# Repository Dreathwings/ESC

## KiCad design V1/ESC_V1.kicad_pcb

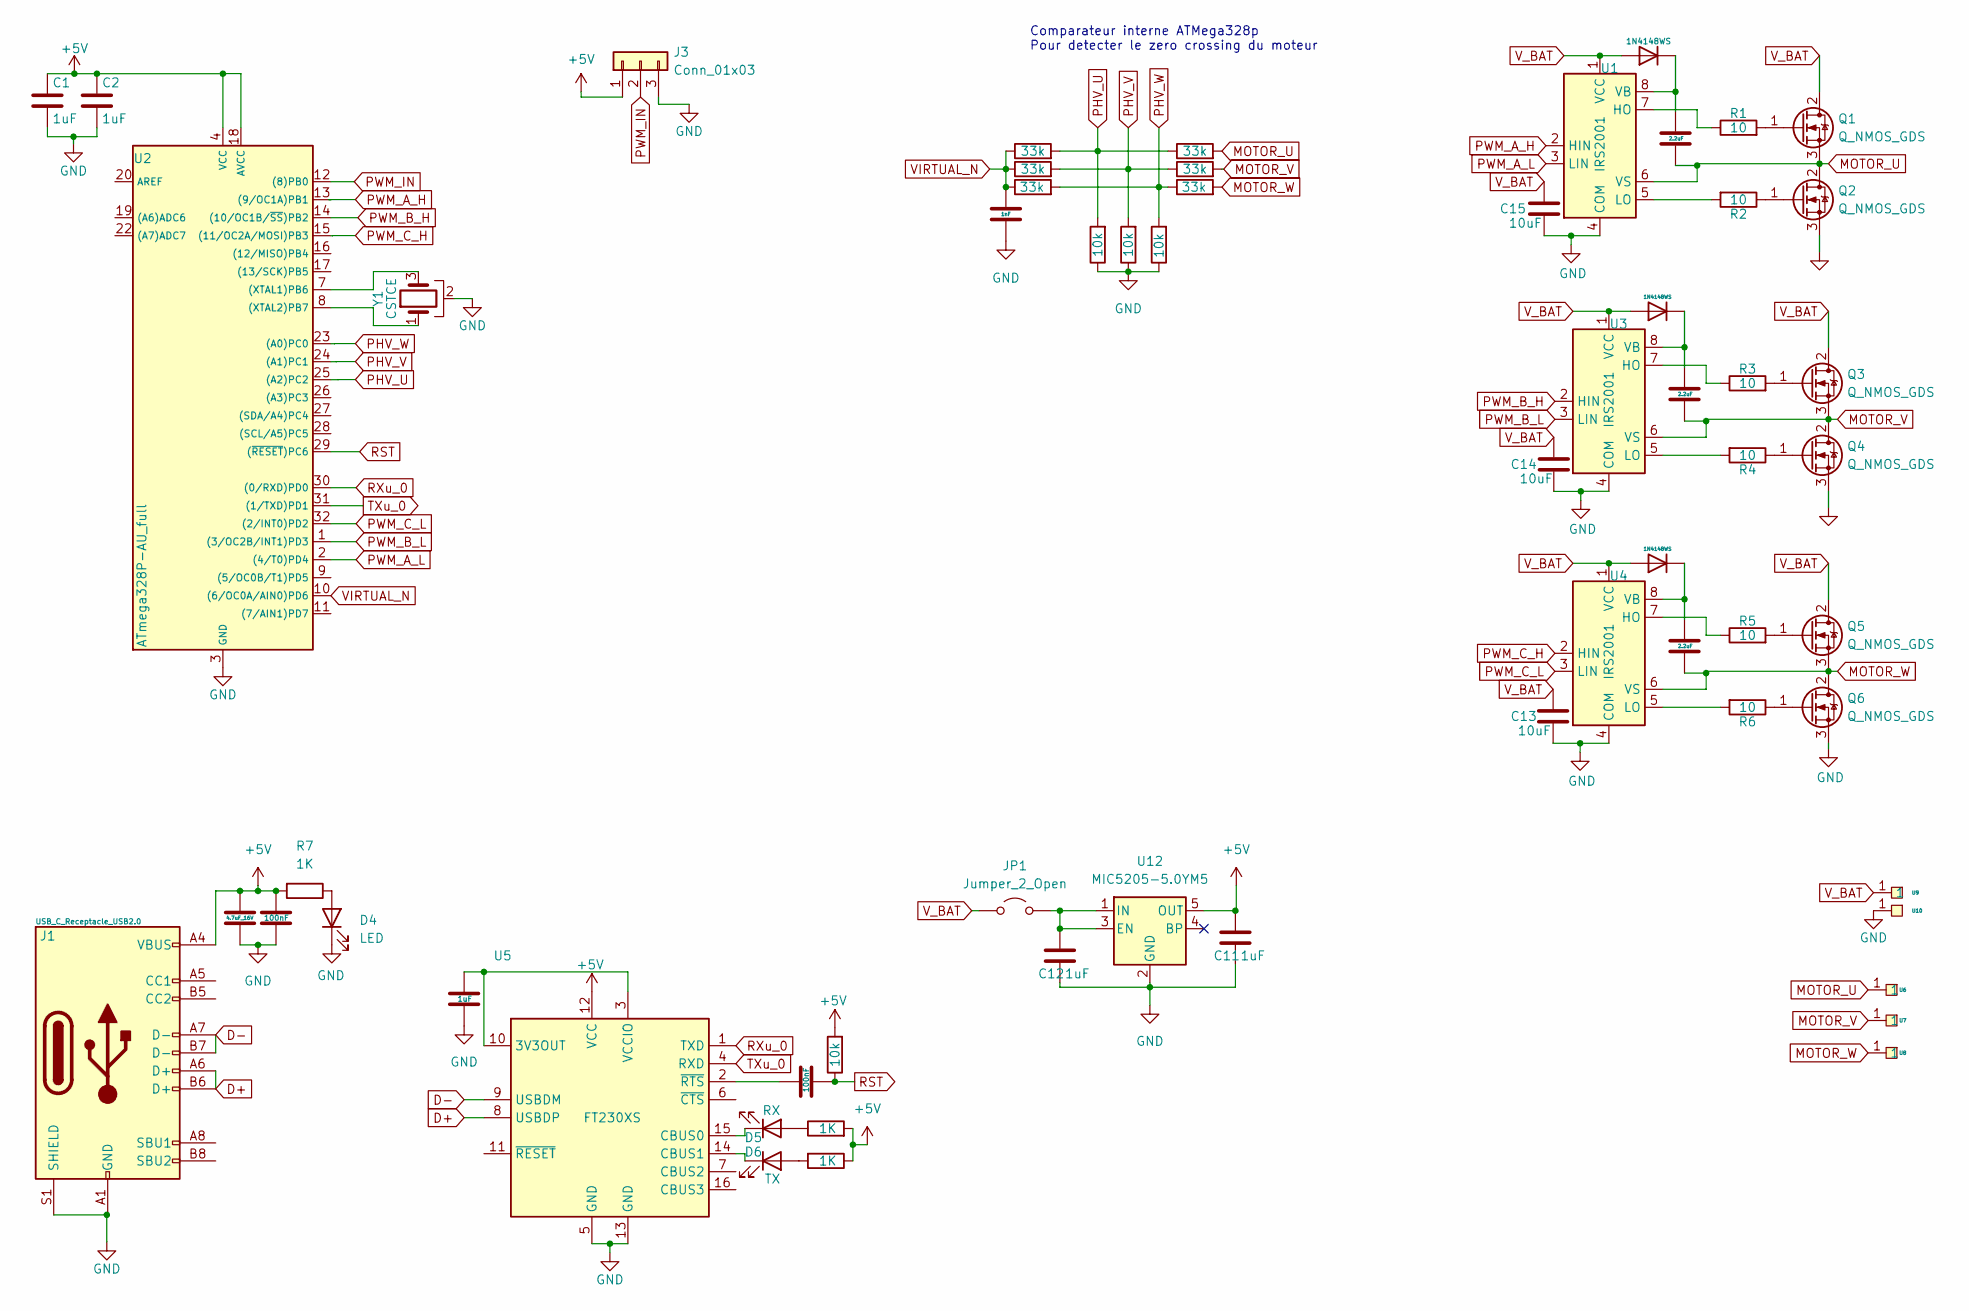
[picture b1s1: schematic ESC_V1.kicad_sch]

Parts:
C1, C2, C11, C12: 1uF; 0603
C3, C4, C5: 2.2uF; 1206
C6: 1uF; 1206
C7, C9: 100nF; 1206
C8: 4.7uF_16V; 1206
C10: 1nF; 1206
C13, C14, C15: 10uF; 1206
D1, D2, D3: 1N4148WS; 1206
D4: LED; 1206
D5: RX; LED_0603_1608Metric
D6: TX; LED_0603_1608Metric
J1: USB_C_Receptacle_USB2.0; USB-C USB4110_GCT
J3: Conn_01x03; PinSocket_1x03_P2.54mm_Horizontal
JP1: Jumper_2_Open; TestPoint_2Pads_Pitch2.54mm_Drill0.8mm
Q1, Q2, Q3, Q4, Q5, Q6: Q_NMOS_GDS; TO-263-2
R1, R2, R3, R4, R5, R6: 10; 1206
R7, R12, R15: 1K; 1206
R8, R9, R10, R11, R13, R14: 33k; 1206
R16, R17, R18, R19: 10k; 1206
U1, U3, U4: IRS2001; SOIC-8_3.9x4.9mm_P1.27mm
U2: ATmega328P-AU_full; TQFP32m
U5: FT230XS; SSOP-16_5.3x6.2mm_P0.65mm
U6, U7, U8, U9, U10: PAD_Connector
U12: MIC5205-5.0YM5; TSOT-23-5
Y1: CSTCE; osc_CSTCE

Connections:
+5V: C1.1, C2.1, C8.1, C9.1, C11.1, J1.A4 (VBUS), J1.A9 (VBUS), J1.B4 (VBUS), J1.B9 (VBUS), J3.1, R7.2, R12.2, R15.1, R19.2, U2.4 (VCC), U2.6 (VCC), U2.18 (AVCC), U5.12 (VCC), U12.5 (OUT)
D+: J1.A6 (D+), J1.B6 (D+), U5.8 (USBDP)
D-: J1.A7 (D-), J1.B7 (D-), U5.9 (USBDM)
GND: C1.2, C2.2, C6.1, C8.2, C9.2, C10.2, C11.2, C12.2, C13.2, C14.2, C15.2, D4.1 (K), J1.A1 (GND), J1.A12 (GND), J1.B1 (GND), J1.B12 (GND), J1.S1 (SHIELD), J3.3, Q2.3 (S), Q4.3 (S), Q6.3 (S), R16.1, R17.1, R18.1, U1.4 (COM), U2.3 (GND), U2.5 (GND), U2.21 (GND), U3.4 (COM), U4.4 (COM), U5.5 (GND), U5.13 (GND), U10.1, U12.2 (GND), Y1.2
MOTOR_U: C3.2, Q1.3 (S), Q2.2 (D), R9.2, U1.6 (VS), U6.1
MOTOR_V: C4.2, Q3.3 (S), Q4.2 (D), R11.2, U3.6 (VS), U7.1
MOTOR_W: C5.2, Q5.3 (S), Q6.2 (D), R14.2, U4.6 (VS), U8.1
unnamed: C3.1, D1.1 (K), U1.8 (VB)
unnamed: C4.1, D2.1 (K), U3.8 (VB)
unnamed: C5.1, D3.1 (K), U4.8 (VB)
unnamed: D4.2 (A), R7.1
unnamed: D5.2 (A), R12.1
unnamed: D5.1 (K), U5.15 (CBUS0)
unnamed: D6.2 (A), R15.2
unnamed: D6.1 (K), U5.14 (CBUS1)
unnamed: C12.1, JP1.2 (B), U12.1 (IN), U12.3 (EN)
unnamed: Q1.1 (G), R1.2
unnamed: Q2.1 (G), R2.1
unnamed: Q3.1 (G), R3.2
unnamed: Q4.1 (G), R4.1
unnamed: Q5.1 (G), R5.2
unnamed: Q6.1 (G), R6.1
unnamed: R1.1, U1.7 (HO)
unnamed: R2.2, U1.5 (LO)
unnamed: U2.7 ((XTAL1)PB6), Y1.3
unnamed: U2.8 ((XTAL2)PB7), Y1.1
unnamed: R3.1, U3.7 (HO)
unnamed: R4.2, U3.5 (LO)
unnamed: R5.1, U4.7 (HO)
unnamed: R6.2, U4.5 (LO)
unnamed: C6.2, U5.3 (VCCIO), U5.10 (3V3OUT)
unnamed: C7.2, U5.2 (~RTS)
PHV_U: R8.2, R9.1, R16.2, U2.25 ((A2)PC2)
PHV_V: R10.2, R11.1, R17.2, U2.24 ((A1)PC1)
PHV_W: R13.2, R14.1, R18.2, U2.23 ((A0)PC0)
PWM_A_H: U1.2 (HIN), U2.13 ((9/OC1A)PB1)
PWM_A_L: U1.3 (LIN), U2.2 ((4/T0)PD4)
PWM_B_H: U2.14 ((10/OC1B/~SS)PB2), U3.2 (HIN)
PWM_B_L: U2.1 ((3/OC2B/INT1)PD3), U3.3 (LIN)
PWM_C_H: U2.15 ((11/OC2A/MOSI)PB3), U4.2 (HIN)
PWM_C_L: U2.32 ((2/INT0)PD2), U4.3 (LIN)
PWM_IN: J3.2, U2.12 ((8)PB0)
RST: C7.1, R19.1, U2.29 ((~RESET)PC6)
RXu_0: U2.30 ((0/RXD)PD0), U5.1 (TXD)
TXu_0: U2.31 ((1/TXD)PD1), U5.4 (RXD)
VIRTUAL_N: C10.1, R8.1, R10.1, R13.1, U2.10 ((6/OC0A/AIN0)PD6)
V_BAT: C13.1, C14.1, C15.1, D1.2 (A), D2.2 (A), D3.2 (A), JP1.1 (A), Q1.2 (D), Q3.2 (D), Q5.2 (D), U1.1 (VCC), U3.1 (VCC), U4.1 (VCC), U9.1

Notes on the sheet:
Comparateur interne ATMega328p Pour detecter le zero crossing du moteur

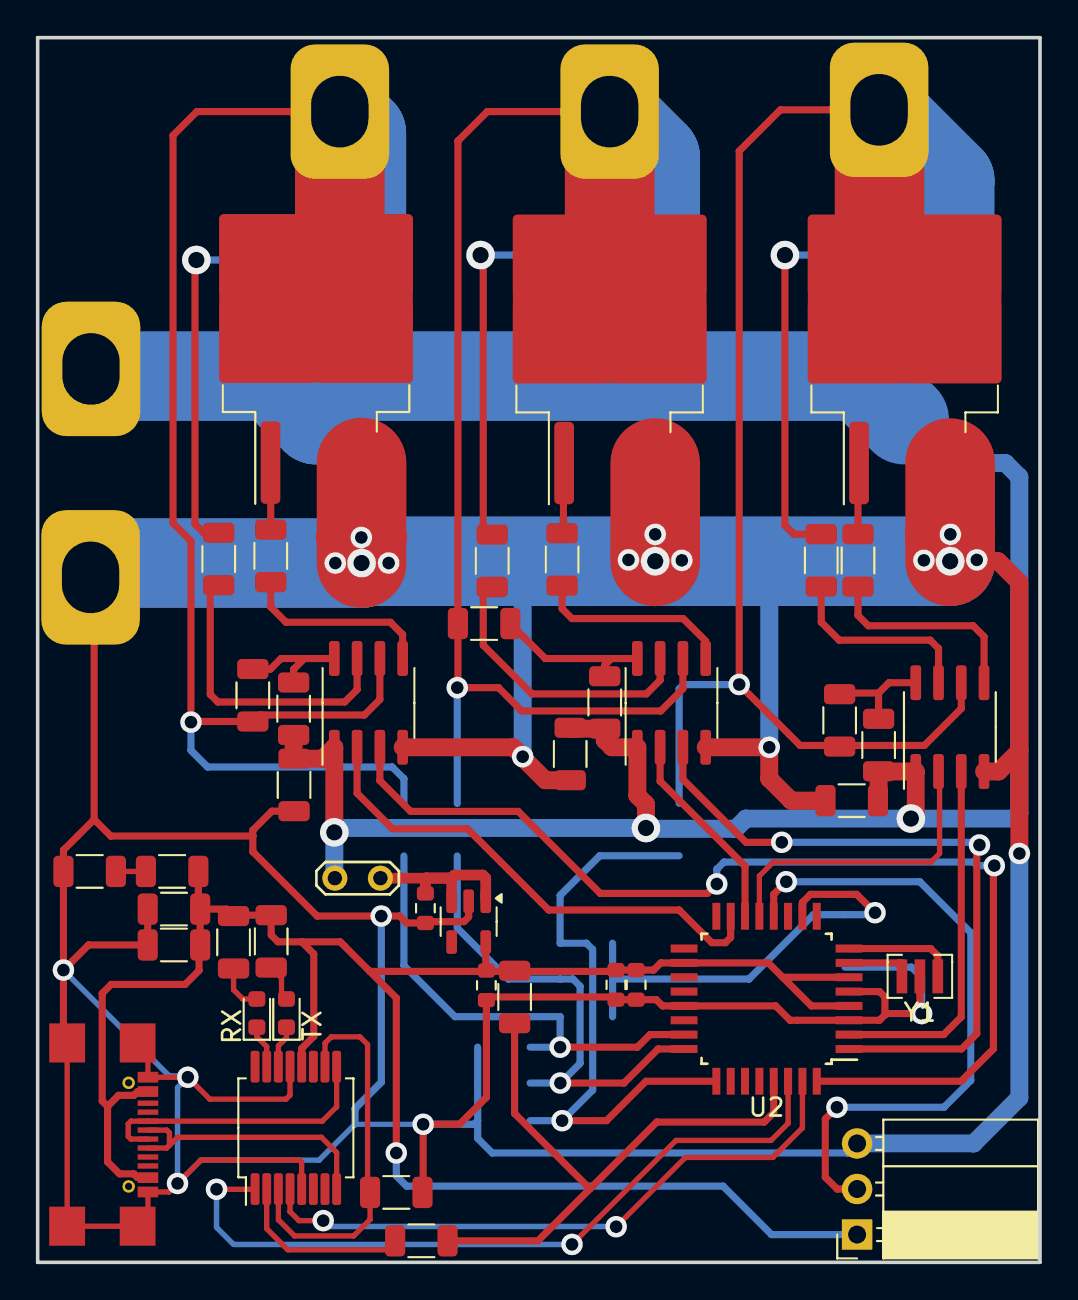
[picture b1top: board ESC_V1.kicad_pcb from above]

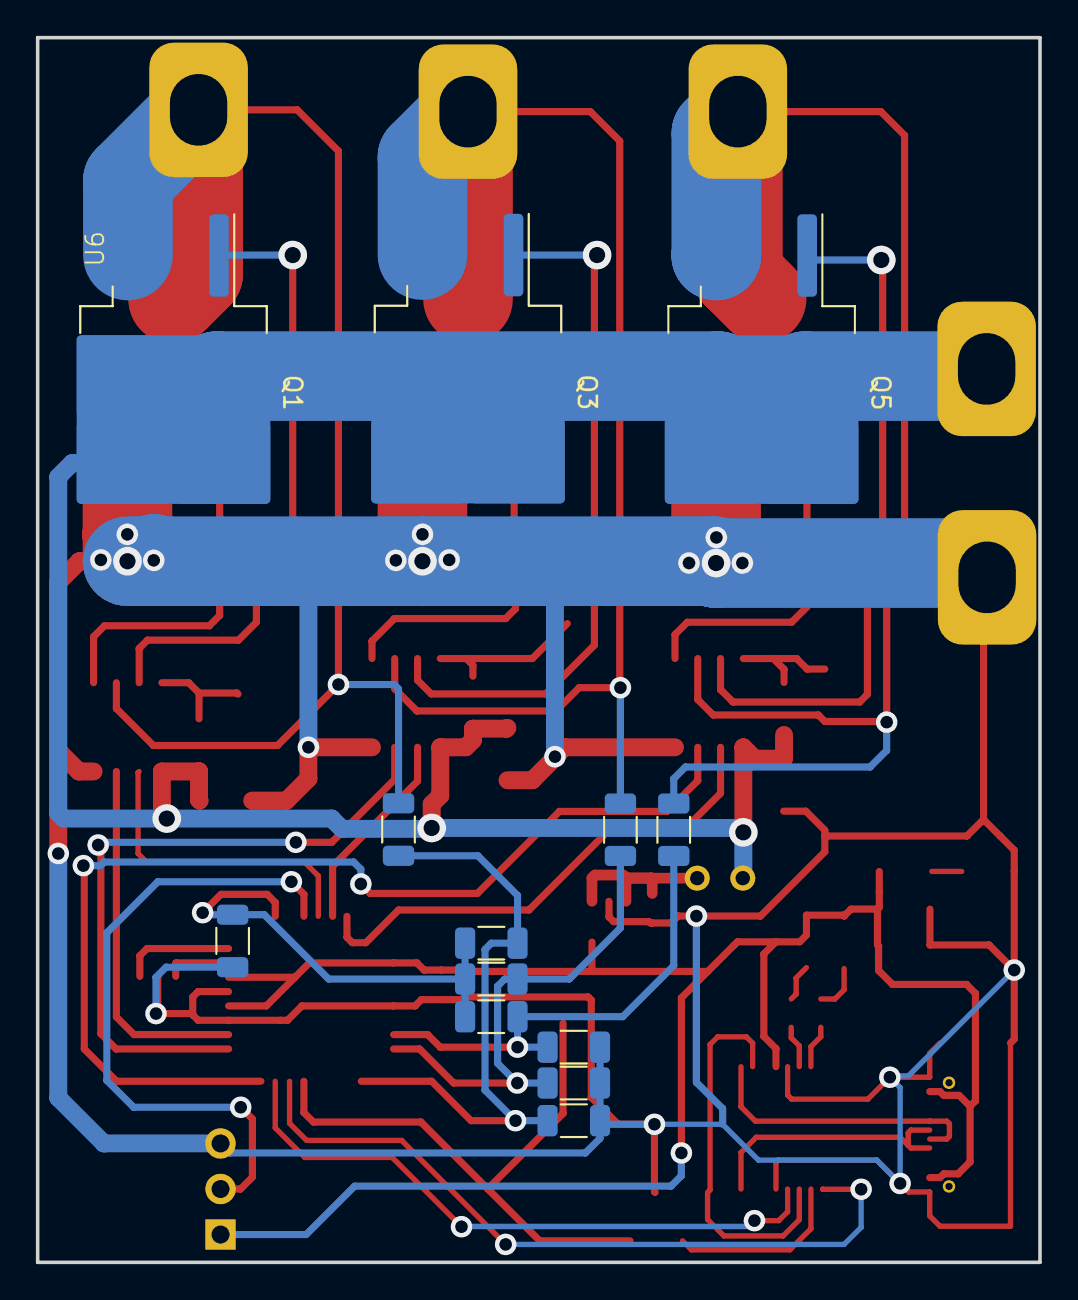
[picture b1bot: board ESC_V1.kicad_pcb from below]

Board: 2 copper layers, 55.9 x 68.3 mm, 61 parts (18 on the bottom side), 47 nets.

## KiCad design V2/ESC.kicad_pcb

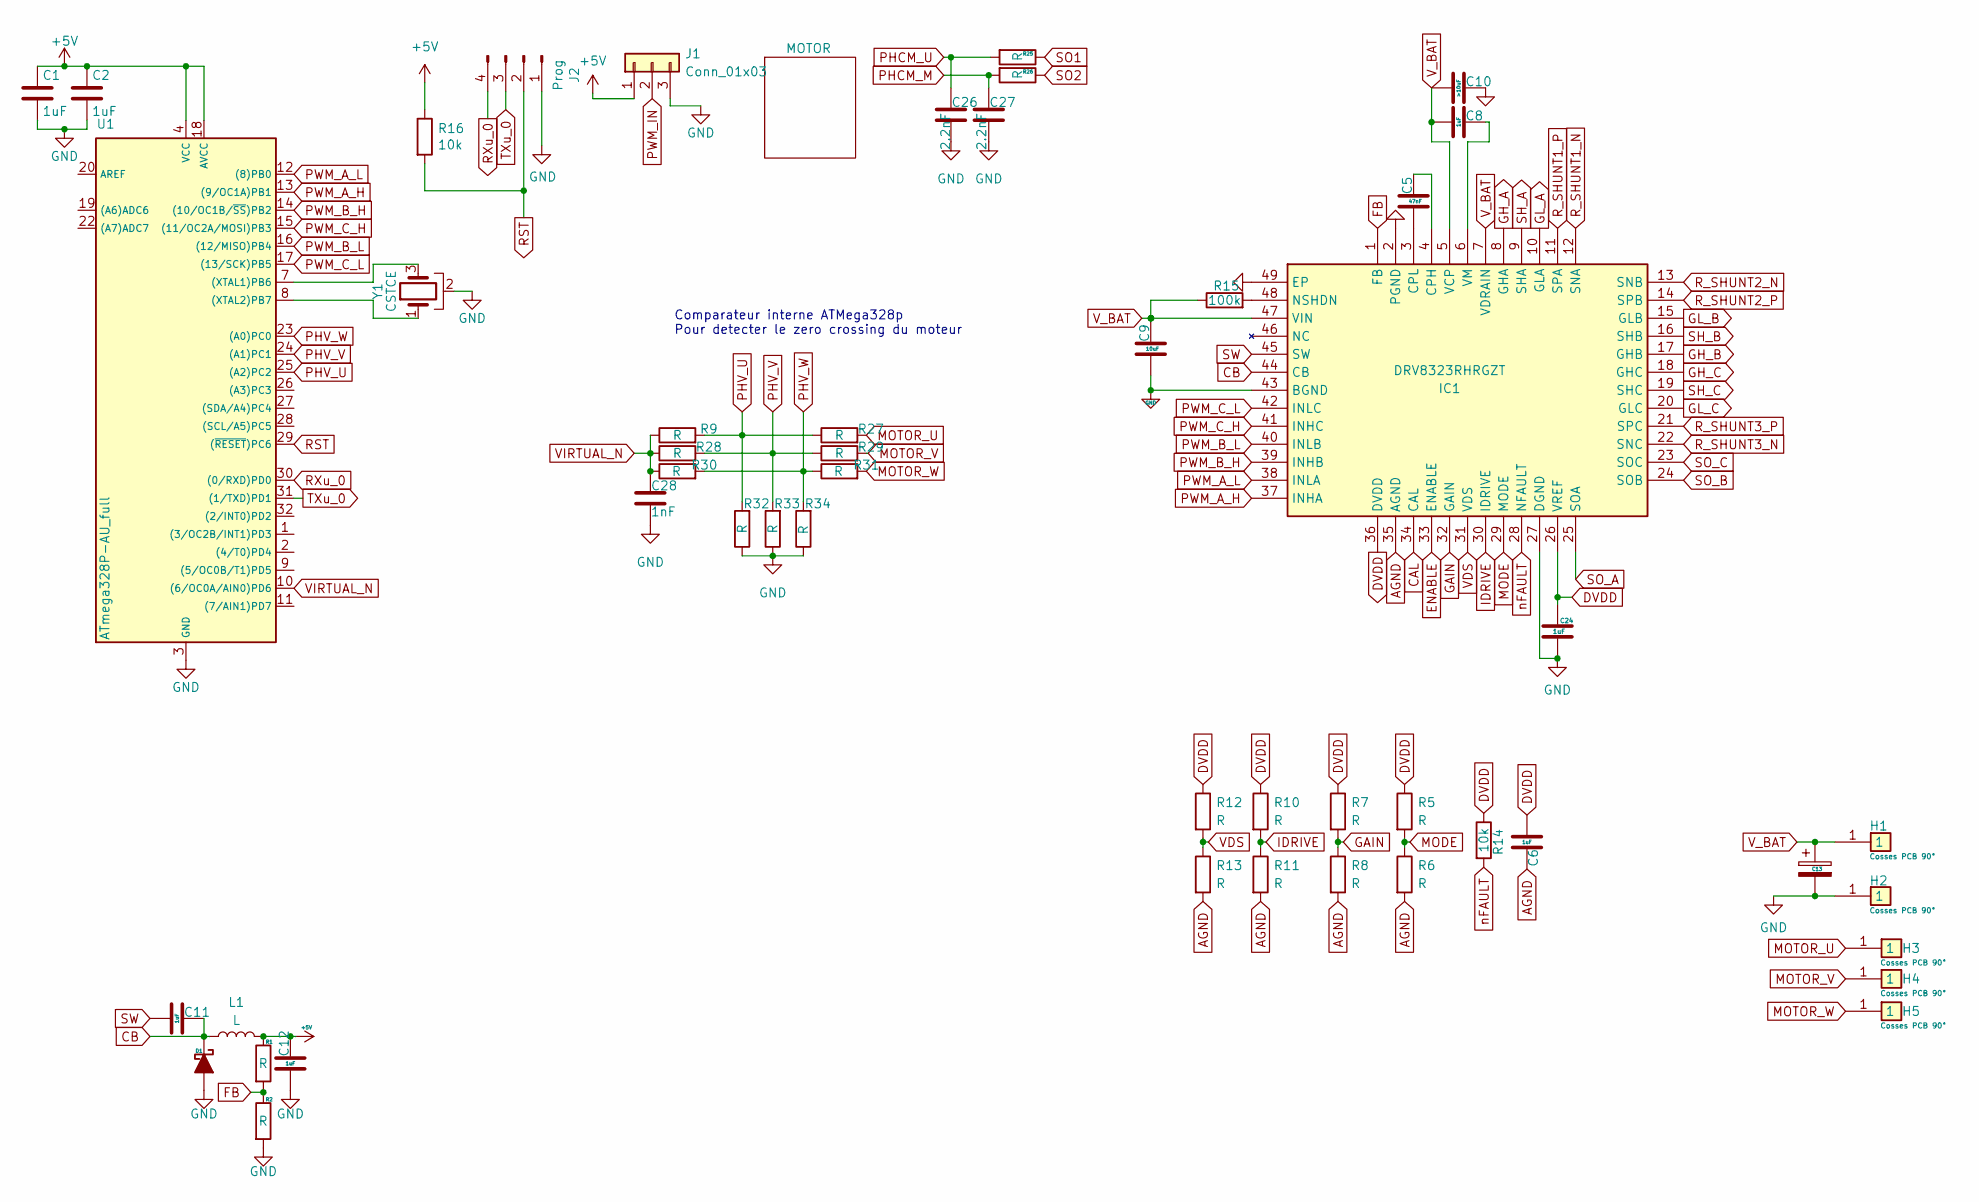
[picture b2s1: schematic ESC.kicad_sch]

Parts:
C1, C2, C8, C11, C12, C24: 1uF; 1206
C5: 47nF; 1206
C6: 1uF; 0603
C9: 10uF; 1206
C10: >10uF; 1206
C13: C_Polarized; CP_Radial_D18.0mm_P7.50mm
C26, C27: 2.2nF; 1206
C28: 1nF; 1206
D1: D_Schottky_Filled; 1206
H1, H2, H3, H4, H5: Cosses PCB 90°; 12177561; Manufacturer_Part_Number 1217756-1
IC1: DRV8323RHRGZT; Mouser Part Number 595-DRV8302DCA
J1: Conn_01x03; PinSocket_1x03_P2.54mm_Horizontal
J2: Prog; PinHeader_1x04_P2.54mm_Vertical
L1: L; L_Ferrocore_DLG-1005
R1, R2, R9, R27, R28, R29, R30, R31, R32, R33, R34: R; 1206
R5, R6, R7, R8, R10, R11, R12, R13, R25, R26: R; 0603
R14: 10k; 0603
R15: 100k; 1206
R16: 10k; 1206
U1: ATmega328P-AU_full; TQFP32m
Y1: CSTCE; osc_CSTCE

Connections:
+5V: C1.1, C2.1, C12.1, J1.1, L1.2, R1.1, R16.1, U1.4 (VCC), U1.6 (VCC), U1.18 (AVCC)
AGND: C6.1, IC1.35 (AGND), R6.2, R8.2, R11.2, R13.2
CAL: IC1.34 (CAL)
CB: C11.1, D1.1 (K), IC1.44 (CB), L1.1
DVDD: C6.2, C24.1, IC1.26 (VREF), IC1.36 (DVDD), R5.1, R7.1, R10.1, R12.1, R14.1
ENABLE: IC1.33 (ENABLE)
FB: IC1.1 (FB), R1.2, R2.1
GAIN: IC1.32 (GAIN), R7.2, R8.1
GH_A: IC1.8 (GHA); also elsewhere on the board
GH_B: IC1.17 (GHB); also elsewhere on the board
GH_C: IC1.18 (GHC); also elsewhere on the board
GL_A: IC1.10 (GLA); also elsewhere on the board
GL_B: IC1.15 (GLB); also elsewhere on the board
GL_C: IC1.20 (GLC); also elsewhere on the board
GND: C1.2, C2.2, C9.2, C10.1, C12.2, C13.2, C24.2, C26.2, C27.2, C28.2, D1.2 (A), H2.1, IC1.2 (PGND), IC1.12 (SNA), IC1.13 (SNB), IC1.22 (SNC), IC1.27 (DGND), IC1.43 (BGND), IC1.49 (EP), J1.3, J2.1, R2.2, R32.1, R33.1, R34.1, U1.3 (GND), U1.5 (GND), U1.21 (GND), Y1.2; also elsewhere on the board
IDRIVE: IC1.30 (IDRIVE), R10.2, R11.1
MODE: IC1.29 (MODE), R5.2, R6.1
MOTOR_U: H3.1, IC1.9 (SHA), R27.2; also elsewhere on the board
MOTOR_V: H4.1, IC1.16 (SHB), R29.2; also elsewhere on the board
MOTOR_W: H5.1, IC1.19 (SHC), R31.2; also elsewhere on the board
unnamed: C5.1, IC1.4 (CPH)
unnamed: C5.2, IC1.3 (CPL)
unnamed: IC1.48 (NSHDN), R15.2
unnamed: C8.1, IC1.6 (VM)
unnamed: U1.7 ((XTAL1)PB6), Y1.3
unnamed: U1.8 ((XTAL2)PB7), Y1.1
PHCM_M: C27.1, R26.2
PHCM_U: C26.1, R25.2
PHV_U: R9.2, R27.1, R32.2, U1.25 ((A2)PC2)
PHV_V: R28.2, R29.1, R33.2, U1.24 ((A1)PC1)
PHV_W: R30.2, R31.1, R34.2, U1.23 ((A0)PC0)
PWM_A_H: IC1.37 (INHA), U1.13 ((9/OC1A)PB1)
PWM_A_L: IC1.38 (INLA), U1.12 ((8)PB0)
PWM_B_H: IC1.39 (INHB), U1.14 ((10/OC1B/~SS)PB2)
PWM_B_L: IC1.40 (INLB), U1.16 ((12/MISO)PB4)
PWM_C_H: IC1.41 (INHC), U1.15 ((11/OC2A/MOSI)PB3)
PWM_C_L: IC1.42 (INLC), U1.17 ((13/SCK)PB5)
PWM_IN: J1.2
RST: J2.2, R16.2, U1.29 ((~RESET)PC6)
RXu_0: J2.4, U1.30 ((0/RXD)PD0)
R_SHUNT1_P: IC1.11 (SPA); also elsewhere on the board
R_SHUNT2_P: IC1.14 (SPB); also elsewhere on the board
R_SHUNT3_P: IC1.21 (SPC); also elsewhere on the board
SO1: R25.1
SO2: R26.1
SO_A: IC1.25 (SOA)
SO_B: IC1.24 (SOB)
SO_C: IC1.23 (SOC)
SW: C11.2, IC1.45 (SW)
TXu_0: J2.3, U1.31 ((1/TXD)PD1)
VDS: IC1.31 (VDS), R12.2, R13.1
VIRTUAL_N: C28.1, R9.1, R28.1, R30.1, U1.10 ((6/OC0A/AIN0)PD6)
V_BAT: C8.2, C9.1, C10.2, C13.1, H1.1, IC1.5 (VCP), IC1.7 (VDRAIN), IC1.47 (VIN), R15.1; also elsewhere on the board
nFAULT: IC1.28 (NFAULT), R14.2

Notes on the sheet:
Comparateur interne ATMega328p Pour detecter le zero crossing du moteur

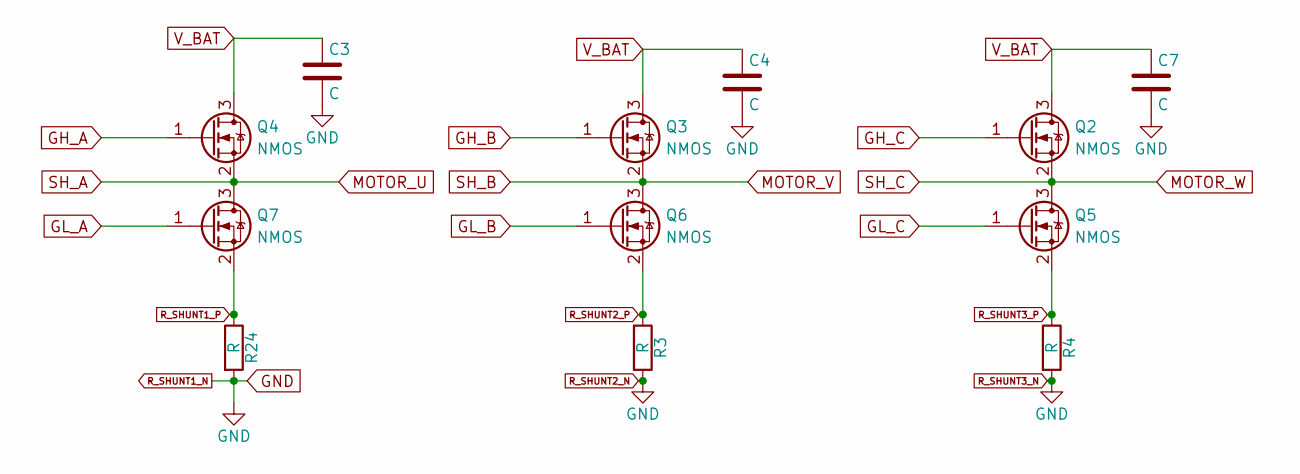
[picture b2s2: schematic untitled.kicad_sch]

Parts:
C3, C4, C7: C; 1206
Q2, Q3, Q4, Q5, Q6, Q7: NMOS; D2PAK
R3, R4, R24: R; R_Shunt_Vishay_WSR2_WSR3

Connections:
GH_A: Q4.1 (G); also elsewhere on the board
GH_B: Q3.1 (G); also elsewhere on the board
GH_C: Q2.1 (G); also elsewhere on the board
GL_A: Q7.1 (G); also elsewhere on the board
GL_B: Q6.1 (G); also elsewhere on the board
GL_C: Q5.1 (G); also elsewhere on the board
GND: C3.2, C4.2, C7.2, R3.2, R4.2, R24.2; also elsewhere on the board
MOTOR_U: Q4.2 (S), Q7.3 (D); also elsewhere on the board
MOTOR_V: Q3.2 (S), Q6.3 (D); also elsewhere on the board
MOTOR_W: Q2.2 (S), Q5.3 (D); also elsewhere on the board
R_SHUNT1_P: Q7.2 (S), R24.1; also elsewhere on the board
R_SHUNT2_P: Q6.2 (S), R3.1; also elsewhere on the board
R_SHUNT3_P: Q5.2 (S), R4.1; also elsewhere on the board
V_BAT: C3.1, C4.1, C7.1, Q2.3 (D), Q3.3 (D), Q4.3 (D); also elsewhere on the board

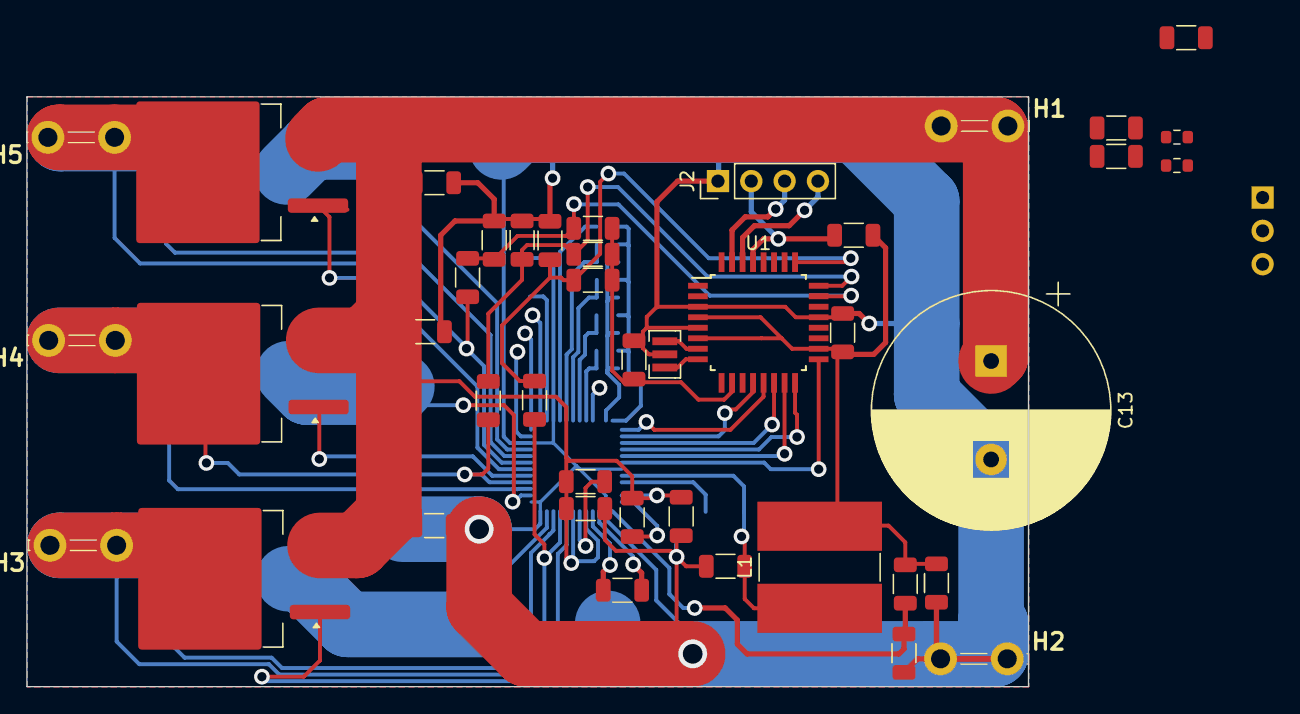
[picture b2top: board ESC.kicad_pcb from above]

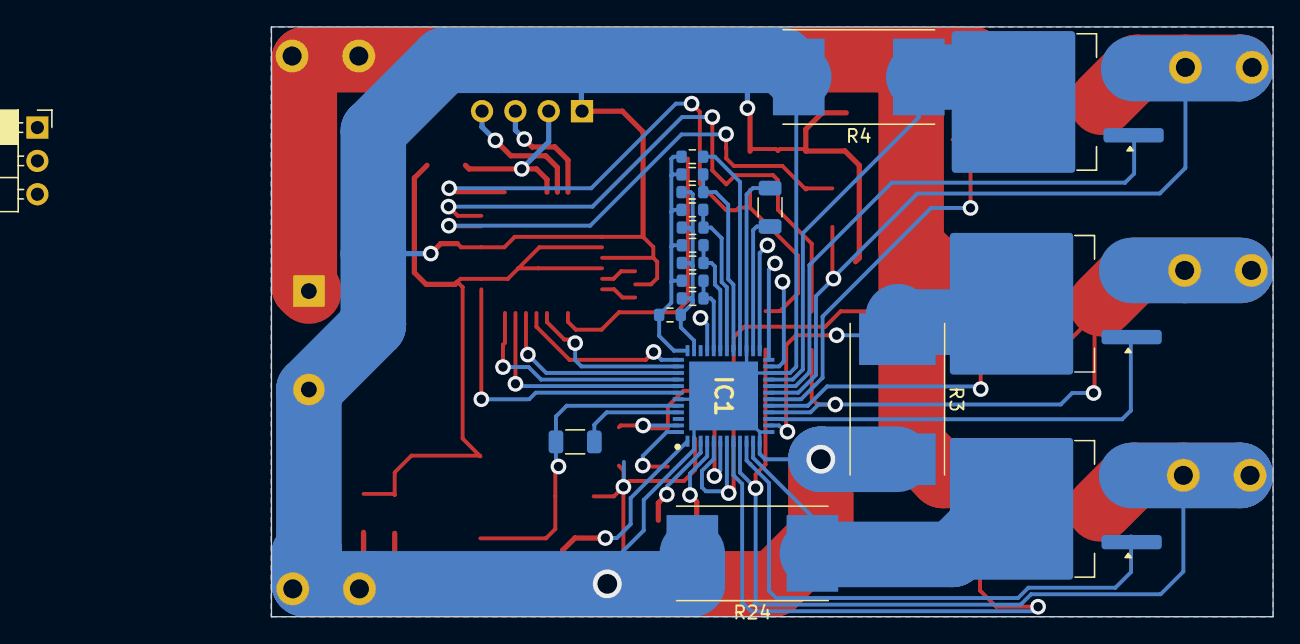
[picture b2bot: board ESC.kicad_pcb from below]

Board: 2 copper layers, 76.3 x 44.9 mm, 62 parts (20 on the bottom side), 46 nets.

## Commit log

2024-06-12 <awawa
2024-06-17 v0.02
2024-06-19 v0.03
2024-07-09 v2 80%
